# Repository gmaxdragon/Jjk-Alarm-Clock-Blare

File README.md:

# JJK Alarm

*A Jujutsu Kaisen-inspired alarm clock made for Hack Club BLARE, by Vivaan Goel.*

## What I made and why

My old alarm clock was really old, looked outdated, and had partly broken. I wanted to replace it with something that actually matched what I liked instead of another plain alarm clock. I looked around online, but I could not find one that looked the way I wanted, so I decided to make my own.

My main inspiration was **Sukuna's Malevolent Shrine** from *Jujutsu Kaisen*. I think it is one of the coolest abilities in the series, and I wanted to turn that shrine style into something I could use every day. The screen shows a hand-sign image with the time underneath it.

## Why there are two PCB versions

The original PCB was too big, so I changed the layout later with AI's help and made this smaller **95 × 95 mm** version. I moved the six buttons into two rows of three, but it still does the same things overall. I kept the original PCB and CAD files too, so you can see what changed.

I also changed the PCB a bit later but forgot to update some of the earlier screenshots. The intended function is the same overall, though. The files in **`PCB/`, `CAD/`, `Firmware/`, and `Production/` are the current compact revision**. The older **125 × 110 mm** version is preserved in [Archive/Original_125x110](Archive/Original_125x110/README.md). The old images are history, not the manufacturing reference.

## The current clock

This is a render of the actual revised CAD geometry, not a photo of a built clock. The electronics are labelled dimensional reference models, not manufacturer-certified component CAD.

## PCB and schematic

The board has two copper layers, a **95 × 95 mm** outline, and **1.6 mm nominal finished thickness**. Nothing was uniformly shrunk. The switches, sockets, pin spacing and drill sizes remain full size. The components were moved and the tracks were routed again.

The XIAO ESP32-C3 reads the six buttons through a three-column, two-row matrix. Each switch has a diode. It updates the TFT over SPI and switches the buzzer through Q1, a 2N3904 transistor. R1 pulls GPIO8 high, R2 limits transistor base current, R3 keeps the buzzer driver off at startup, and the capacitors filter the 3.3 V rail.

The compact board uses the **same component-to-net connections and GPIO assignments** as the original rectangular circuit. Native KiCad ERC, DRC, schematic/PCB matching, and unconnected-pad checks pass under the saved check settings. See [the reports](Production/Checks/).

### Button layout, looking at the front

| Left | Middle | Right |
| --- | --- | --- |
| UP (SW1) | TIME SET (SW3) | SNOOZE (SW5) |
| DOWN (SW2) | CLOCK SET (SW4) | ALARM ON (SW6) |

Horizontal switch pitch is **19.05 mm**. The two rows are **22 mm** apart. The compact version uses six normal kit keycaps. My earlier tall printed cap extensions are preserved with the original version, but are not used on this one.

## CAD and assembly

I did my original case work in **Tinkercad**, using a shrine model from **MakerWorld**, my own changes, and ideas from friends. I am not claiming I modeled the original shrine from scratch. Later, AI helped repair the exported geometry and add a new electronics mount and removable front panel for the smaller PCB.

The current complete model is [CAD/JJK_Alarm_Assembly.step](CAD/JJK_Alarm_Assembly.step). It includes the shrine body and integrated carrier, removable front panel, display retainer, drilled PCB, component reference models and fastener references, all placed together. It reopened as **50 valid solids**. The sculptural part is a faceted solid, not a reconstructed editable Tinkercad history.

The separate print files are in [Production/Case_Parts](Production/Case_Parts/). There are **three case parts**: the shrine body with its integrated electronics carrier, the front panel, and the display retainer. Do not print the reference electronics or the old tall keycaps for this revision.

The PCB screws into four supports. The display sits in a pocket behind the front panel and has a removable retaining bar. The back has a USB-cable passage and a zip-tie saddle for strain relief. The front has holes for the buzzer sound. This version does not depend on an unspecified USB-C panel-mount extension.

The decorative shrine remains approximately **339 × 339 × 287 mm**, so it needs a sufficiently large printer or a separately planned print split. Making the PCB smaller did not automatically make the shrine smaller. The decorative skin was remeshed on a 1 mm grid to remove touching/nonmanifold surfaces, which slightly softens fine details. The precise mounting features were added afterward. The untouched owner upload is preserved in [CAD/Owner_Originals](CAD/Owner_Originals/).

The CAD clearance checks use reference dimensions, including a **21.08 × 73.15 × 3.7 mm TFT envelope**. They are not measurements of a received display. Physical assembly, connector fit, tolerances and alarm loudness still require testing. Detailed dimensions and assembly order are in [CAD/README.md](CAD/README.md).

## Firmware

The code is in [Firmware/JJK_Alarm](Firmware/JJK_Alarm/), for the **Seeed XIAO ESP32-C3** using Arduino and Adafruit GFX/ST7789. The portrait screen is **76 × 284 pixels**. The image is stored in the firmware and appears above the stacked hours and minutes.

The code includes Wi-Fi time synchronization, manual clock/date setting, selectable alarm weekdays, five-minute snooze, dismissal, a countdown timer, stopwatch, themes, and a local phone settings page. These are implemented features, not a claim that the assembled clock has been hardware-tested.

| Button | Function |
| --- | --- |
| UP | Increase a value or move through choices |
| DOWN | Decrease a value; hold at home for the stopwatch |
| TIME SET | Edit the clock/date; hold for status |
| CLOCK SET | Edit the alarm and weekdays; hold for the countdown |
| SNOOZE | Snooze for five minutes; hold to dismiss |
| ALARM ON | Toggle the alarm; hold to change the theme |

The current firmware compiles for ESP32-C3 and passes the host-side alarm/timer tests. **The committed first-power configuration keeps the buzzer silent until its wiring and electrical behavior have been checked.** Do not mistake a successful compile for a sound test.

Power is through the XIAO's USB-C connector. There is no internal battery or backup RTC, so a total power loss stops the clock. The PCB also keeps the TFT backlight on rather than switching it in firmware. Setup and first-power instructions are in [Firmware/README.md](Firmware/README.md).

## What still needs checking before I call it finished

The digital files are checked, but I have not printed and assembled this compact version yet. The shrine STL is still **339 × 339 × 287 mm**, and I have confirmed my printer can fit it. A split design is not needed for my printer.

I also still need to check the actual display, buzzer, sockets, USB plug, screw access, wiring space and full button travel against the case. The display model uses reference dimensions. The saved collision checks cover the PCB/components against the carrier and front panel; they do not prove cable routing, moving-part travel or every interface in the complete assembled clock.

The PCB matrix connections match the firmware: GPIO5/6/7 select the three columns and GPIO8/9 read the two rows. The diode cathodes face the switches. An independent directed-connectivity model now passes all 64 combinations of pressed switches, with no ghost keys or key-order mismatch. I still need to test all six buttons, debounce, simultaneous presses and boot/reset behavior on the real board. The alarm/timer tests do not test the physical matrix.

The buzzer stays disabled with the supplied settings. I need to verify its type, current and polarity, Q1 pinout, sound and the display wiring/offsets before enabling it. The clock also needs a supervised alarm/snooze test and a power-loss/restart test. The original shrine and artwork source links/licenses still need completing in the attribution file. So this is a design-review package, and I am **not claiming full submission readiness or a tested working build**.

## Parts for one clock

This BOM describes the compact design. It is not a list of parts already purchased or fitted.

| Part | Quantity | Purpose |
| --- | ---: | --- |
| Custom 95 × 95 mm, two-layer PCB, 1.6 mm finished | 1 | Current compact board |
| Seeed XIAO ESP32-C3 | 1 | Microcontroller and USB-C power |
| 1×7, 2.54 mm female socket strips | 2 | J1/J2 |
| Compatible 1×7 male header strips | 2 | Mount the XIAO in the sockets |
| 2.25-inch ST7789 TFT, 76 × 284 pixels | 1 | Display |
| 1×8, 2.54 mm male header | 1 | J3 |
| Female-to-female jumper wires | 8 | Display wiring |
| MX-compatible switches | 6 | SW1-SW6 |
| Normal compatible 1U DSA keycaps | 6 | The compact version's buttons |
| 1N4148 diodes | 6 | D1-D6 |
| 1N4148 diode | 1 optional | D7, only when appropriate for the actual buzzer |
| 3.3 V buzzer | 1 | BZ1; 12 mm/7.6 mm lead-pitch footprint provision |
| 2N3904 transistor | 1 | Q1 |
| 10 kΩ resistor | 1 | R1 |
| 1 kΩ resistor | 1 | R2 |
| 100 kΩ resistor | 1 | R3 |
| 10 µF electrolytic capacitor | 1 | C1 |
| 100 nF ceramic capacitor | 1 | C2 |
| Printed shrine body, front panel and display retainer | 1 each | Three production case parts |
| M3 × 8 mm screws | 4 | PCB supports |
| M3 × 16 mm screws | 6 | Four front-panel and two display-retainer fasteners |
| M3 hex nuts, nominal 5.5 mm across flats | 10 | Captured fasteners |
| Nonconductive soft shim, about 0.5 mm | 1 | Display retention without hard pressure on glass |
| Nylon zip tie, about 2.5 mm wide | 1 | USB-cable strain relief |
| Reputable 5 V USB adapter and suitable USB-C cable | 1 set | External power |

Some items are extra to the basic kit, including sockets, the transistor/passives, nuts, two additional M3 × 16 mm screws, the shim and power accessories. Exact purchased-part dimensions and prices are not being claimed. The buzzer footprint describes the design, not a measurement of the shipped buzzer.

## Challenges and AI assistance

I spent a lot of time making the PCB and schematic with my friend, arranging parts, fixing errors, and changing the CAD. It got pretty frustrating at times, but I wanted to get it working rather than stop halfway through.

Just giving you a heads up, **AI was used in this project**. My friend and I did the hands-on work on the original PCB and schematic, and AI helped explain things and give me ideas. I did the original Tinkercad modifications using some MakerWorld models because modeling the whole shrine myself was too hard.

Since I cannot code by myself yet, I worked with AI to make the firmware through some back and forth. AI also helped document and upload the project to GitHub, rearrange and route the smaller PCB, repair the exports, and create the new compact mounting parts. I am not claiming those later changes were all hand-designed by me.

The story in this README comes from my voice typing. AI helped organize and format it and check the technical descriptions. I understand if the organizers ask for changes or return it. This is the best I can do right now, and I have learned a lot from working through it. Thank you so much in advance.

## Stardance recording note

By the way, I forgot to click **Publish to Stardance** when recording the timelapses of the PCB and schematic. I clicked **Public**, though, so I am not sure whether they will be attached. So sorry about that! Thank you!

## Project files

| Folder | Contents |
| --- | --- |
| [CAD](CAD/README.md) | Complete placed assembly STEP, checks, reference geometry and original source |
| [PCB](PCB/) | Current matching KiCad project, schematic and compact PCB |
| [Firmware](Firmware/README.md) | Arduino source, artwork and setup instructions |
| [Production](Production/README.md) | Current `gerbers.zip`, drill reports and three case-part exports |
| [Docs](Docs/SUBMISSION_CHECK.md) | Submission inventory, images and test evidence |
| [Archive/Original_125x110](Archive/Original_125x110/README.md) | Preserved original rectangular design, CAD and manufacturing files |

Use the current folders together. Do not mix the original Gerbers, compact PCB and old case openings. The submission files are prepared for technical review; successful file checks do not prove physical safety or guarantee Hack Club acceptance.

## Credits and future ideas

Thanks to Hack Club BLARE for the project and kit, to my friend for working on the PCB and schematic with me, and to the friends who gave me suggestions. The shrine uses a MakerWorld model and the screen uses artwork I supplied. The exact original model/artist links and license details have not yet been established, so I have not invented a creator credit. See [Docs/ATTRIBUTION.md](Docs/ATTRIBUTION.md).

Later, I would like to try a bigger screen and real audio playback hardware. The current buzzer is for tones, not voices or music.

<details>
<summary>My original screenshots before the compact revision</summary>

These remain unmodified history images. The current compact PCB and CAD are shown above.
</details>

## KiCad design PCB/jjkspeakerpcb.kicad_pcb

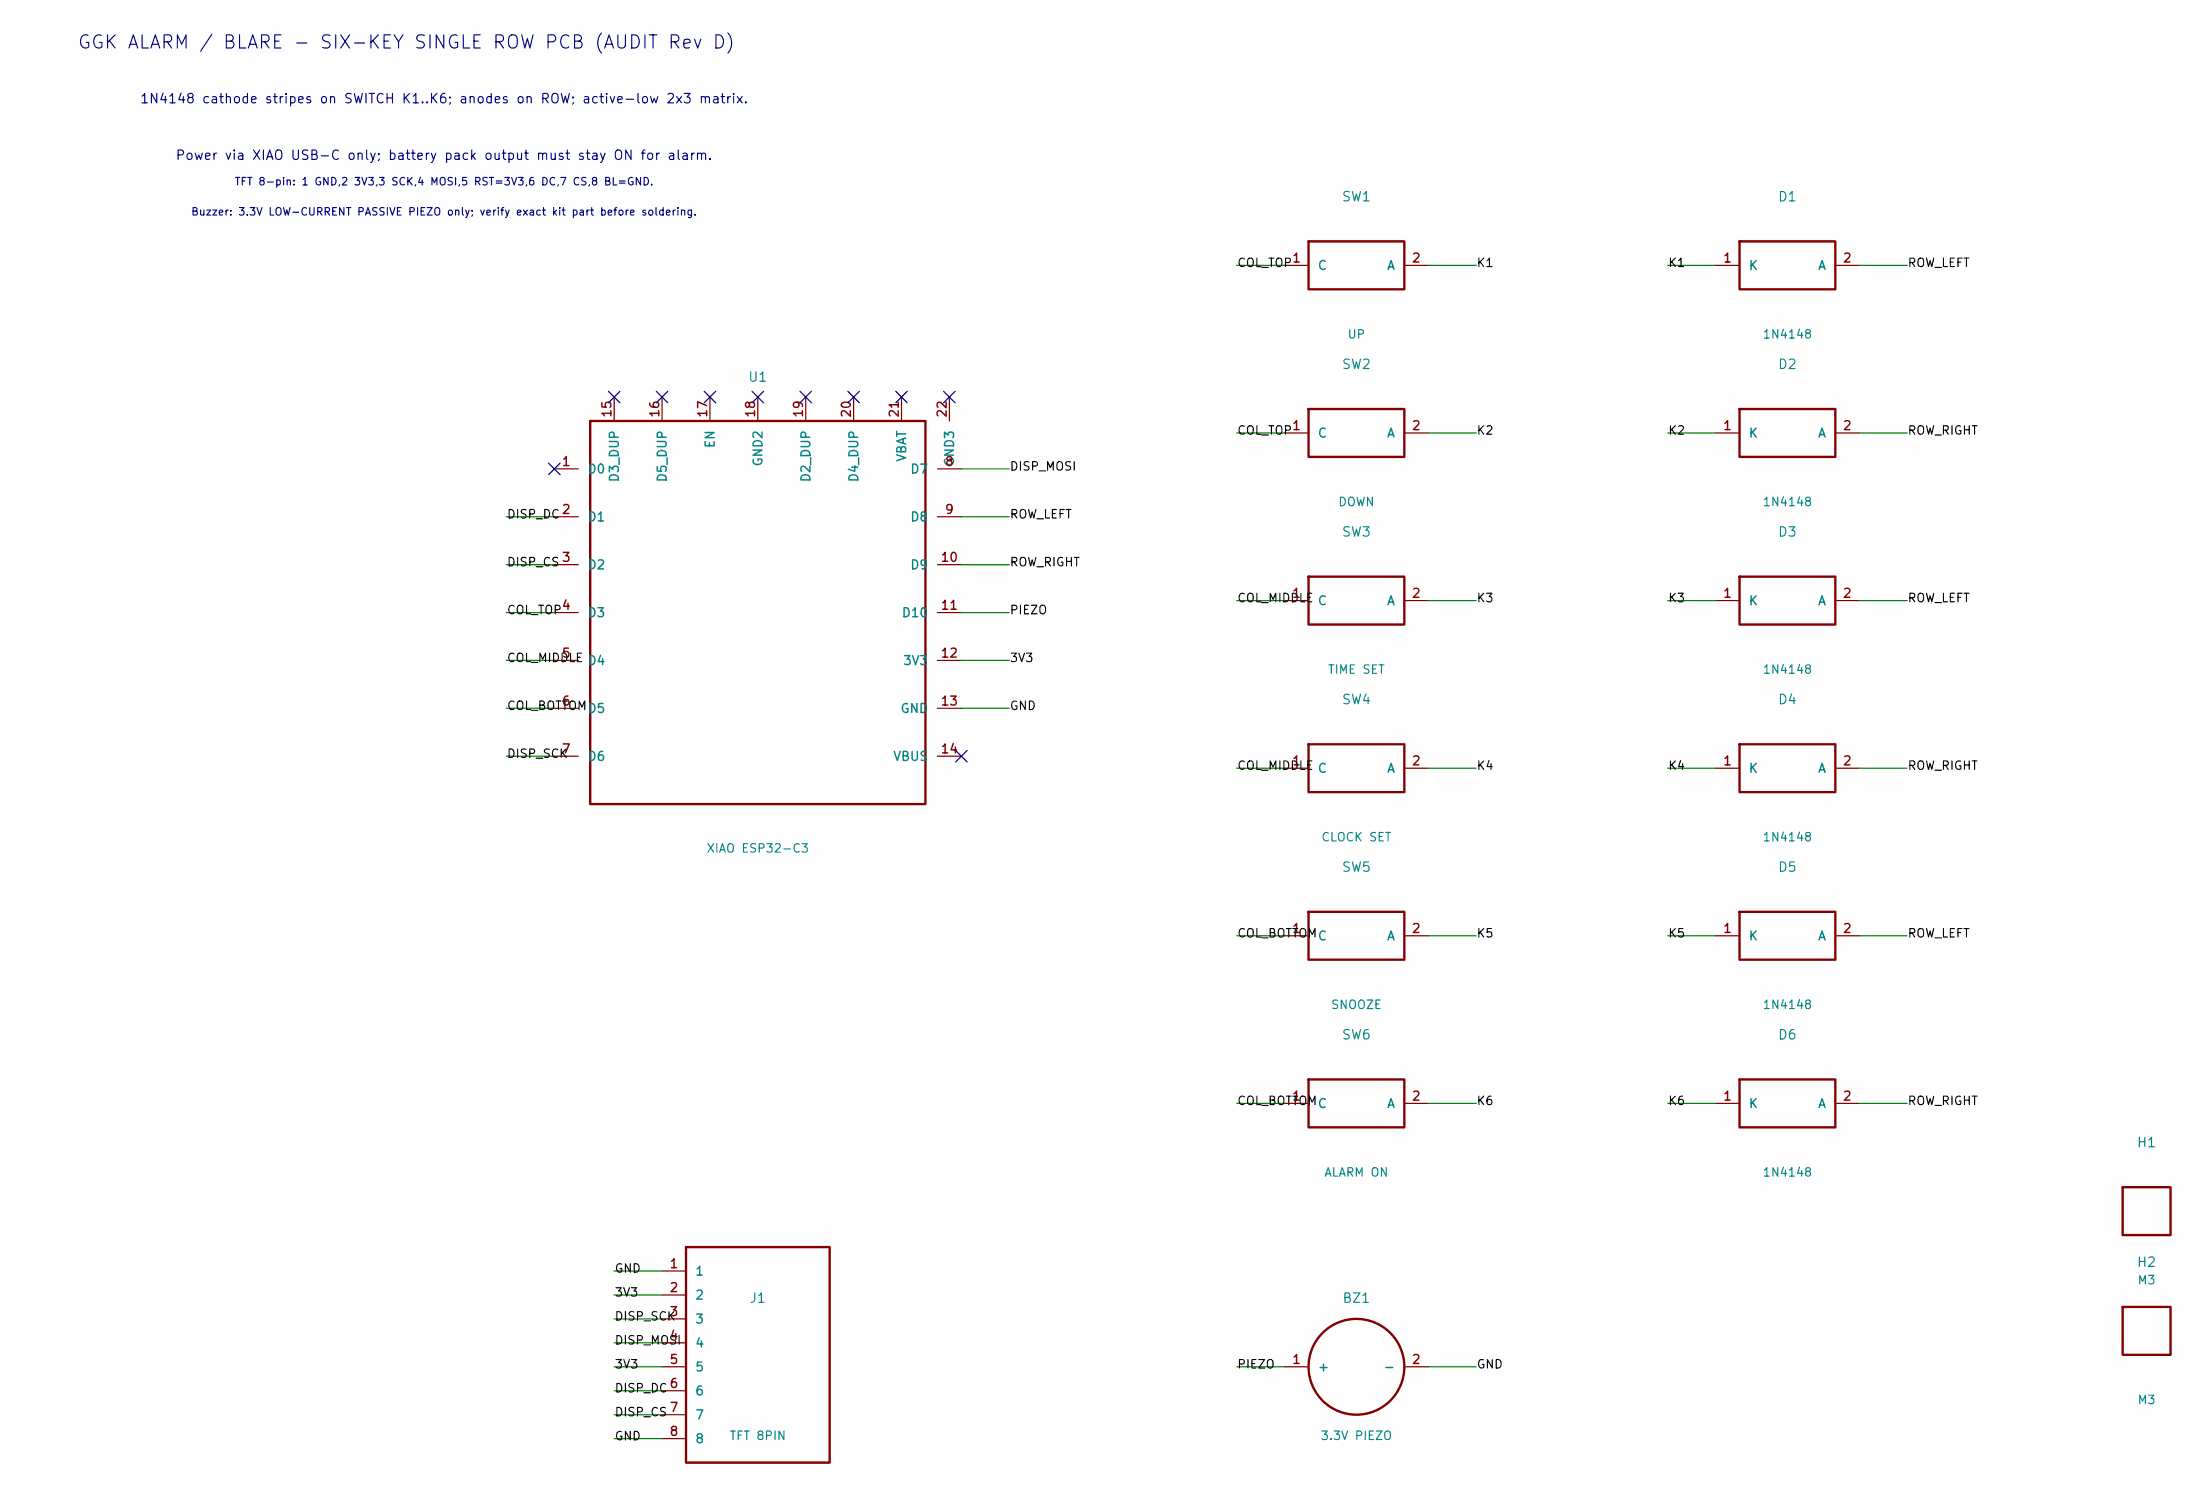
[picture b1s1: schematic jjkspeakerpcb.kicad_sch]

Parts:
BZ1: 3.3V PIEZO; Piezo_P12_P7.62
D1, D2, D3, D4, D5, D6: 1N4148; D_DO35_P7.62
H1, H2: M3; MountingHole_3.2
J1: TFT 8PIN; PinHeader_1x08_2.54
SW1: UP; MX_1U_PCB
SW2: DOWN; MX_1U_PCB
SW3: TIME SET; MX_1U_PCB
SW4: CLOCK SET; MX_1U_PCB
SW5: SNOOZE; MX_1U_PCB
SW6: ALARM ON; MX_1U_PCB
U1: XIAO ESP32-C3; Seeed_XIAO_ESP32C3_Castellated

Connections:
/3V3: J1.2, J1.5, U1.12 (3V3)
/COL_BOTTOM: SW5.1 (C), SW6.1 (C), U1.6 (D5)
/COL_MIDDLE: SW3.1 (C), SW4.1 (C), U1.5 (D4)
/COL_TOP: SW1.1 (C), SW2.1 (C), U1.4 (D3)
/DISP_CS: J1.7, U1.3 (D2)
/DISP_DC: J1.6, U1.2 (D1)
/DISP_MOSI: J1.4, U1.8 (D7)
/DISP_SCK: J1.3, U1.7 (D6)
/GND: BZ1.2 (-), J1.1, J1.8, U1.13 (GND)
/K1: D1.1 (K), SW1.2 (A)
/K2: D2.1 (K), SW2.2 (A)
/K3: D3.1 (K), SW3.2 (A)
/K4: D4.1 (K), SW4.2 (A)
/K5: D5.1 (K), SW5.2 (A)
/K6: D6.1 (K), SW6.2 (A)
/PIEZO: BZ1.1 (+), U1.11 (D10)
/ROW_LEFT: D1.2 (A), D3.2 (A), D5.2 (A), U1.9 (D8)
/ROW_RIGHT: D2.2 (A), D4.2 (A), D6.2 (A), U1.10 (D9)

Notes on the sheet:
GGK ALARM / BLARE - SIX-KEY SINGLE ROW PCB (AUDIT Rev D)
1N4148 cathode stripes on SWITCH K1..K6; anodes on ROW; active-low 2x3 matrix.
Power via XIAO USB-C only; battery pack output must stay ON for alarm.
TFT 8-pin: 1 GND,2 3V3,3 SCK,4 MOSI,5 RST=3V3,6 DC,7 CS,8 BL=GND.
Buzzer: 3.3V LOW-CURRENT PASSIVE PIEZO only; verify exact kit part before soldering.

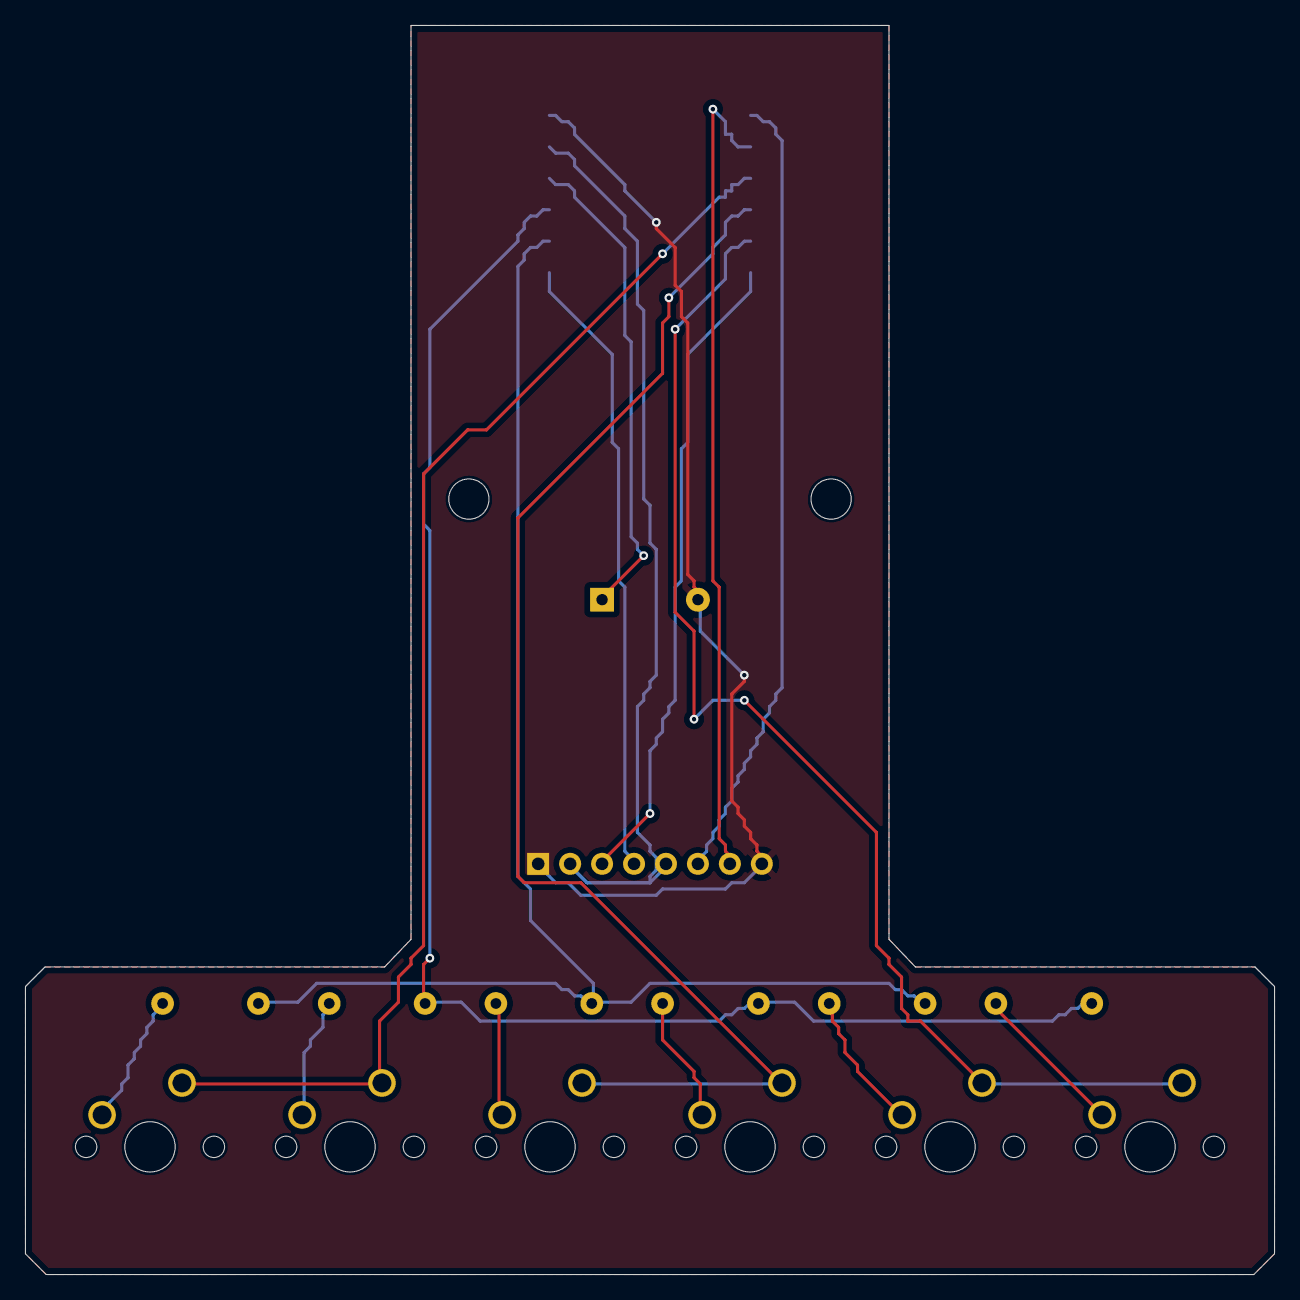
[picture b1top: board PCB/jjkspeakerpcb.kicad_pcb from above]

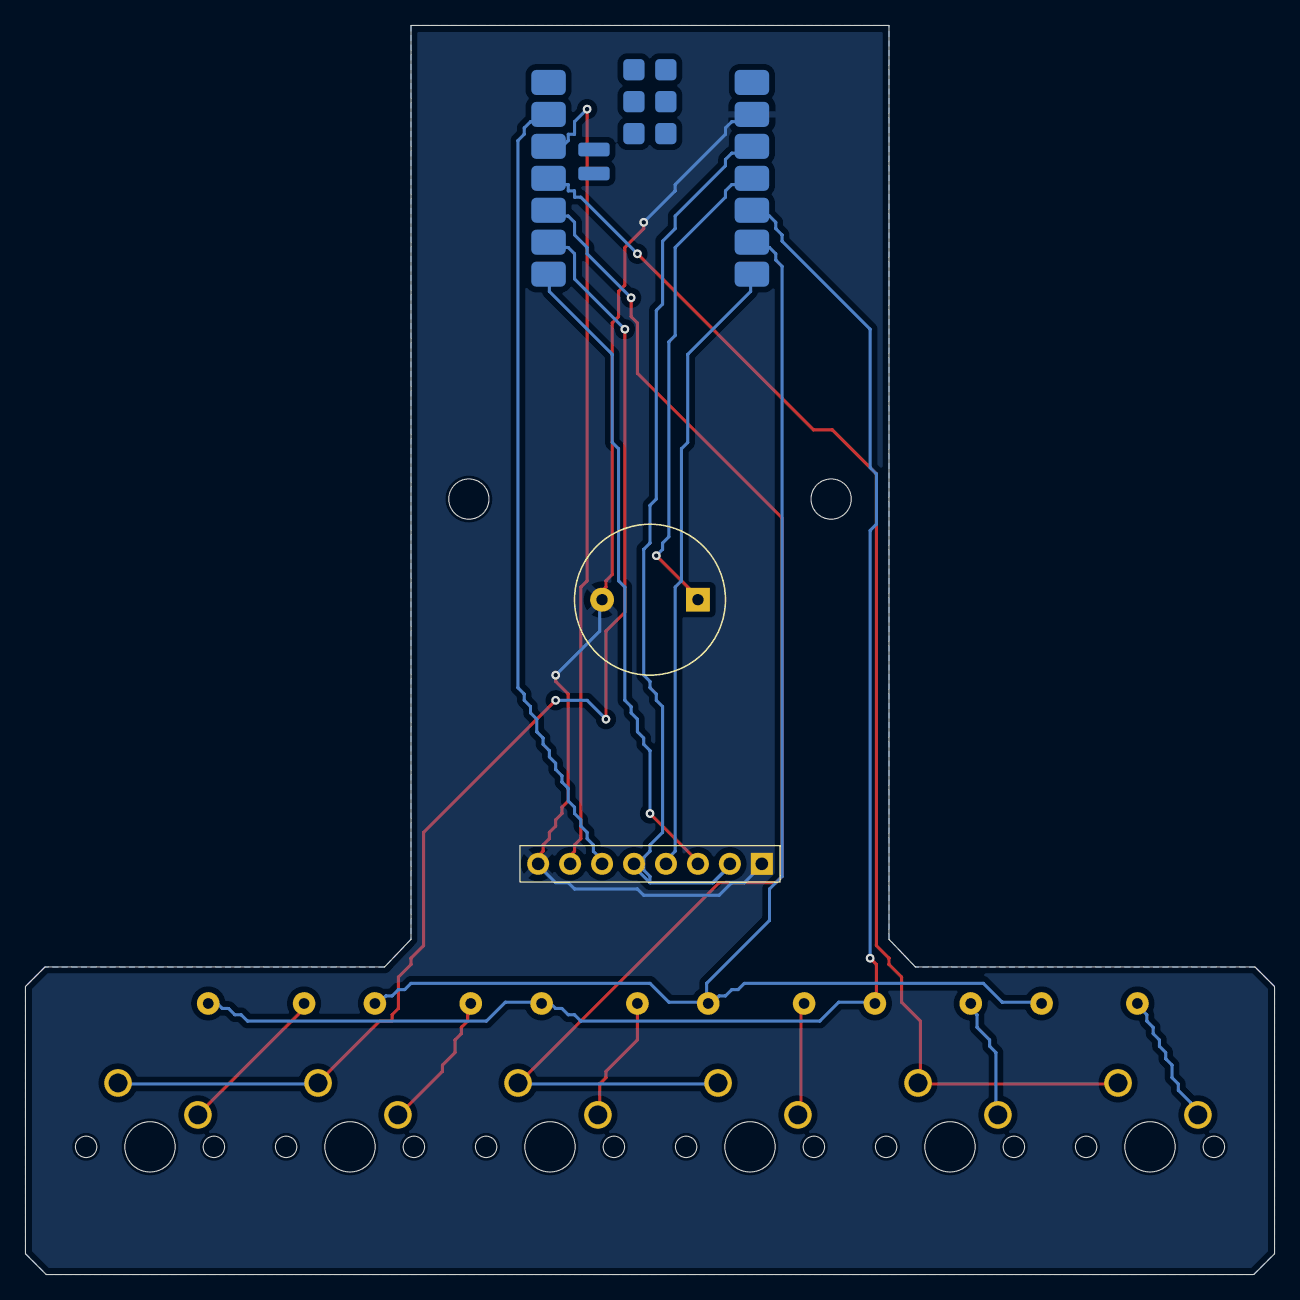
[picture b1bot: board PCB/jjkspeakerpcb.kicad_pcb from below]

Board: 2 copper layers, 99.3 x 99.3 mm, 17 parts (9 on the bottom side), 18 nets.

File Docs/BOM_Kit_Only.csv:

Reference,Quantity,Part,From_BLARE_Kit,Mount,Verification_Gate
U1,1,Seeed Studio XIAO ESP32-C3 with built-in USB-C,YES,PCB back near top,Check castellated solder joints and access to USB-C
J1,1,8-pin 2.54mm male header,YES,PCB back below TFT region,Verify pin order and jumper orientation
TFT1,1,2.25-inch ST7789 76x284 portrait TFT module,YES,Off-board front via 8 F-F jumper wires,Verify actual supplied module current and dimensions
SW1-SW6,6,MX keyboard switch,YES,One 15.9mm-spaced row on front,Actual housing/keycap fit MUST PASS
D1-D6,6,1N4148 through-hole diode DO-35,YES,PCB back along switches,Bar pad1 towards individual switch K signal
BZ1,1,3.3V low-current passive piezo (PROVISIONAL),YES,PCB back,Exact kit part type/current must be verified before solder/enable
H1-H2,2,M3 mechanical hole 3.2mm,PCB CUTOUT,Through PCB,Support keyboard bar in the printed case; ensure metal screw heads clear copper
CAP1-CAP6,6,Custom <=15.4mm MX keycaps with GGK design,USER PRINTS,Above switches,Stock DSA full width NOT compatible
USB_C_CABLE,1,Certified USB-C cable/adapter or USB power bank,NOT IN KIT,USB port on XIAO,Test power supply and current
BATTERY,0,No internal battery (not in kit),NOT IN KIT,NONE,USB unplugged means board off

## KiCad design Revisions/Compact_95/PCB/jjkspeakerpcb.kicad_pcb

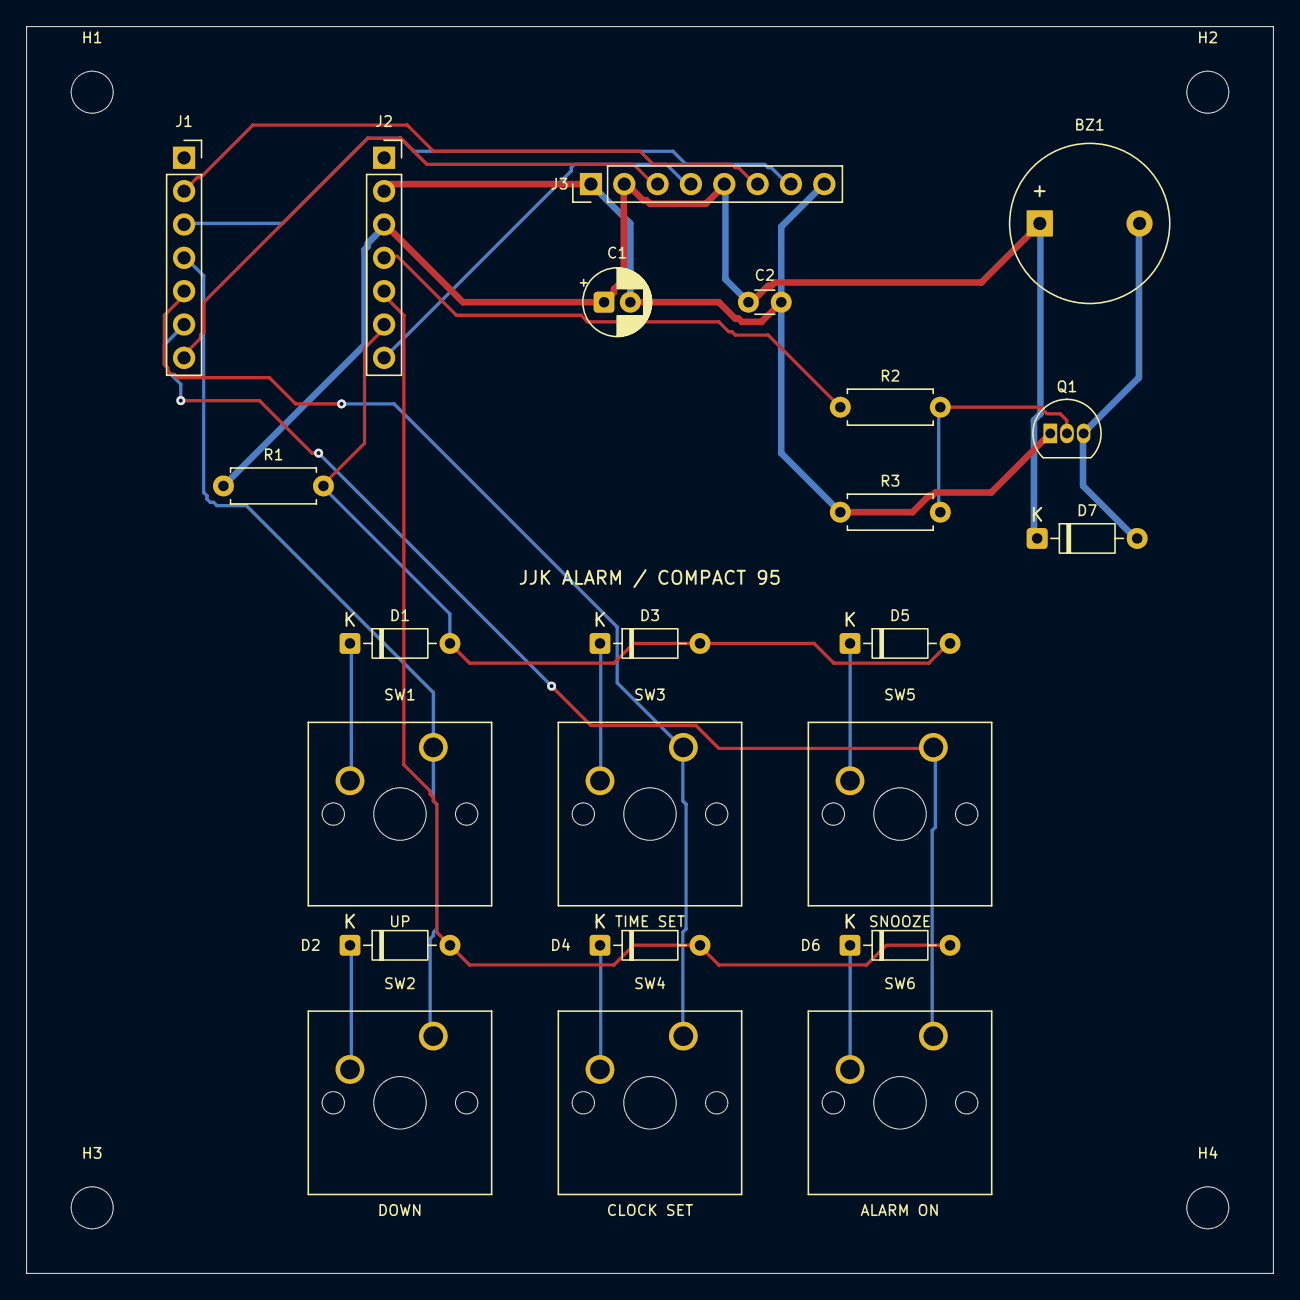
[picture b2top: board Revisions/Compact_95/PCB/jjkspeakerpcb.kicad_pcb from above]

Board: 2 copper layers, 95.0 x 95.0 mm, 27 parts (0 on the bottom side), 20 nets.

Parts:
BZ1: Buzzer_3.3V; Buzzer_12x9.5RM7.6
C1: 10uF; CP_Radial_D5.0mm_P2.00mm
C2: 100nF; C_Disc_D3.0mm_W1.6mm_P2.50mm
D1, D2, D3, D4, D5, D6, D7: 1N4148; D_DO-35_SOD27_P7.62mm_Horizontal
H1, H2, H3, H4: MountingHole; MountingHole_3.2mm_M3
J1: XIAO_LEFT; PinSocket_1x07_P2.54mm_Vertical
J2: XIAO_RIGHT; PinSocket_1x07_P2.54mm_Vertical
J3: TFT_8PIN; PinHeader_1x08_P2.54mm_Vertical
Q1: 2N3904; TO-92_Inline
R1: 10k; R_Axial_DIN0207_L6.3mm_D2.5mm_P7.62mm_Horizontal
R2: 1k; R_Axial_DIN0207_L6.3mm_D2.5mm_P7.62mm_Horizontal
R3: 100k; R_Axial_DIN0207_L6.3mm_D2.5mm_P7.62mm_Horizontal
SW1: UP; SW_Cherry_MX_1.00u_PCB
SW2: DOWN; SW_Cherry_MX_1.00u_PCB
SW3: TIME SET; SW_Cherry_MX_1.00u_PCB
SW4: CLOCK SET; SW_Cherry_MX_1.00u_PCB
SW5: SNOOZE; SW_Cherry_MX_1.00u_PCB
SW6: ALARM ON; SW_Cherry_MX_1.00u_PCB

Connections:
+3V3: BZ1.1 (+), C1.1, C2.1, D7.1 (K), J2.3, J3.2, J3.5, R1.1
/10: J2.4, R2.1
/BOT: J1.6, SW5.1, SW6.1
/CS: J1.3, J3.7
/DC: J1.2, J3.6
/DISP_MOSI: J2.7, J3.4
/DISP_SCK: J1.7, J3.3
/LEFT: D1.2 (A), D3.2 (A), D5.2 (A), J2.6, R1.2
/MID: J1.5, SW3.1, SW4.1
/NEG: BZ1.2 (-), D7.2 (A), Q1.3 (C)
/RIGHT: D2.2 (A), D4.2 (A), D6.2 (A), J2.5
/TOP: J1.4, SW1.1, SW2.1
GND: C1.2, C2.2, J2.2, J3.1, J3.8, Q1.1 (E), R3.1
unnamed: D1.1 (K), SW1.2
unnamed: D2.1 (K), SW2.2
unnamed: D3.1 (K), SW3.2
unnamed: D4.1 (K), SW4.2
unnamed: D5.1 (K), SW5.2
unnamed: D6.1 (K), SW6.2
unnamed: Q1.2 (B), R2.2, R3.2
